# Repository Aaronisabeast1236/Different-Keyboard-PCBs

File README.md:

All of these files contain different Kicad keyboard PCBs and Schematics.
None of the files have have a microcontroller in them so they can not simply be downloaded and sent off to get printed, however they are ready for someone to put in and wire up a microcontroller
I am making these files because I could not find any templates online so I just decided to learn how to do it myself and share them with other people.
At some point I'd like to take suggestions and eventually add them to this repsitory.

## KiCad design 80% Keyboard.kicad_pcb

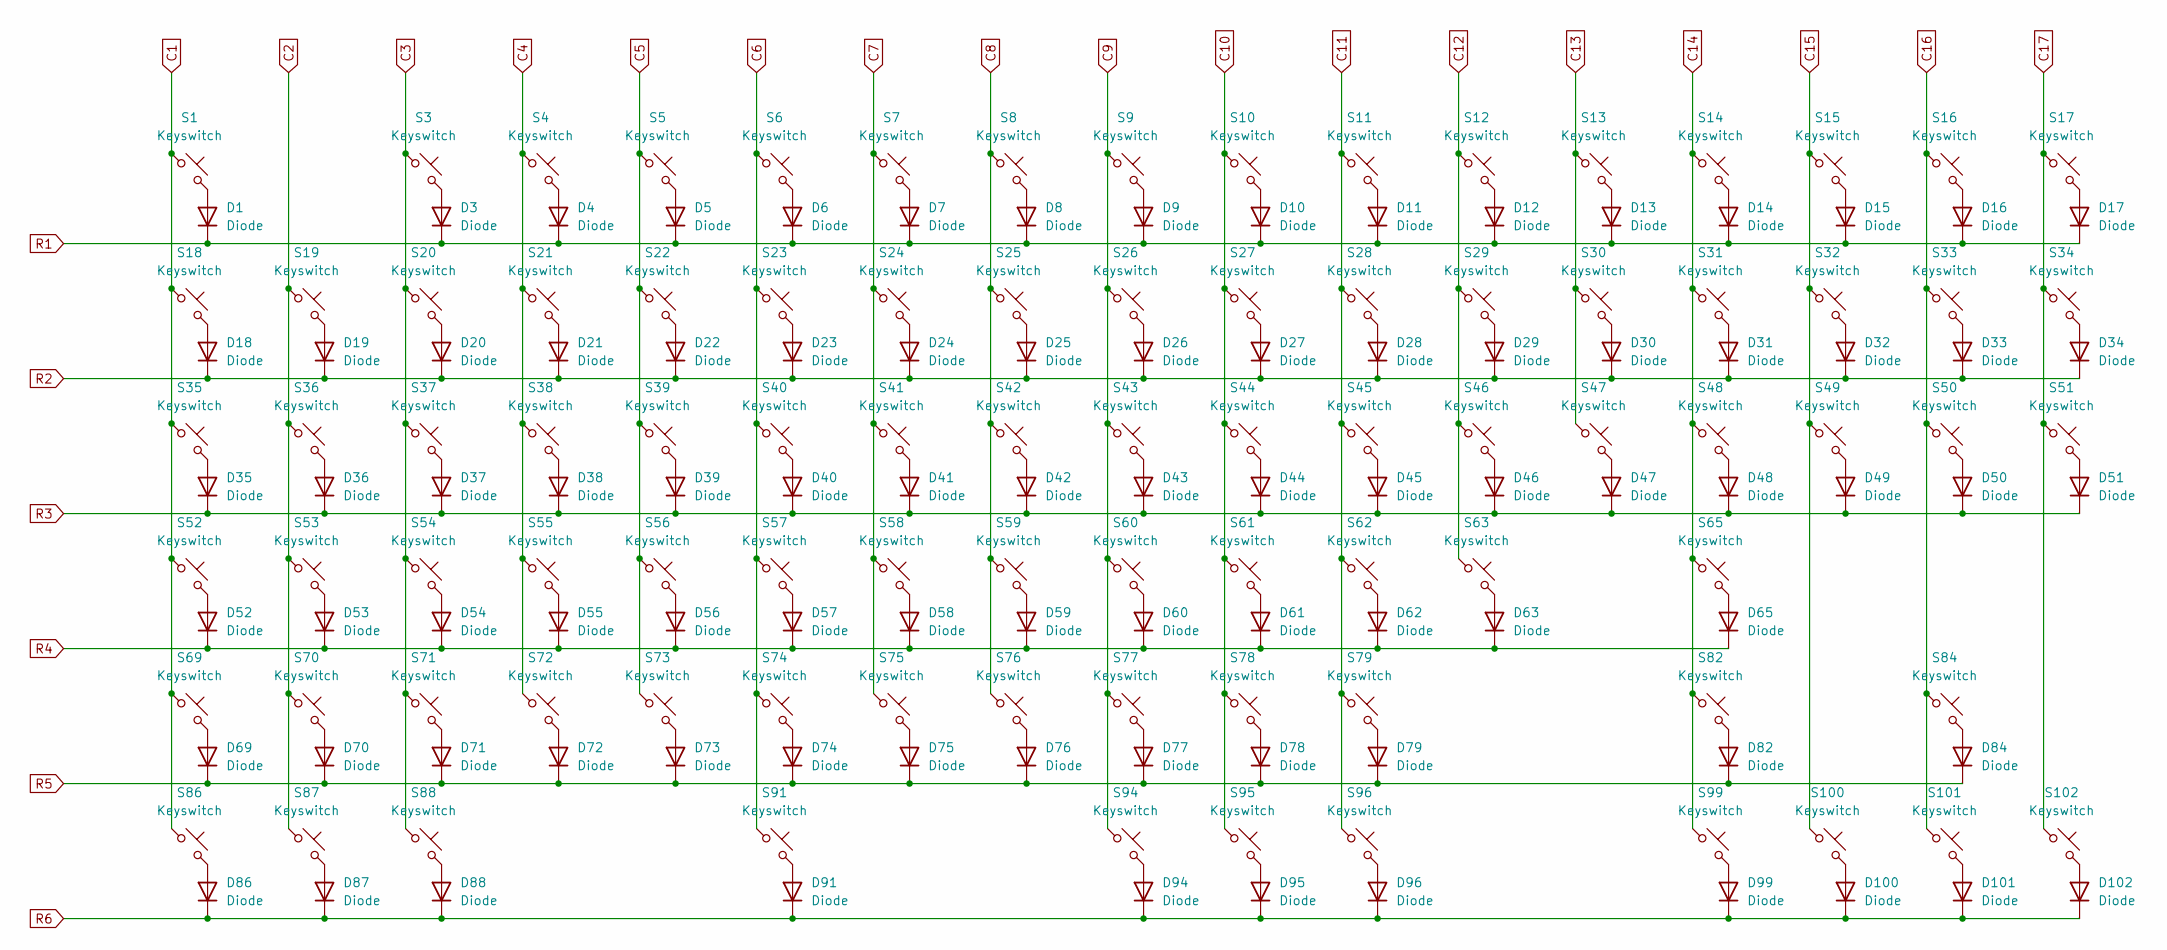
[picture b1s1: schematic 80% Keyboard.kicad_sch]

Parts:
D1, D3, D4, D5, D6, D7, D8, D9, D10, D11, D12, D13, D14, D15, D16, D17, D18, D19, D20, D21, D22, D23, D24, D25, D26, D27, D28, D29, D30, D31, D32, D33, D34, D35, D36, D37, D38, D39, D40, D41, D42, D43, D44, D45, D46, D47, D48, D49, D50, D51, D52, D53, D54, D55, D56, D57, D58, D59, D60, D61, D62, D63, D65, D69, D70, D71, D72, D73, D74, D75, D76, D77, D78, D79, D82, D84, D86, D87, D88, D91, D94, D95, D96, D99, D100, D101, D102: Diode; Diode_SOD-123
S1, S3, S4, S5, S6, S7, S8, S9, S10, S11, S12, S13, S14, S15, S16, S17, S18, S19, S20, S21, S22, S23, S24, S25, S26, S27, S28, S29, S30, S32, S33, S34, S36, S37, S38, S39, S40, S41, S42, S43, S44, S45, S46, S47, S49, S50, S51, S53, S54, S55, S56, S57, S58, S59, S60, S61, S62, S63, S70, S71, S72, S73, S74, S75, S76, S77, S78, S79, S84, S100, S101, S102: Keyswitch; MX_PCB_1.00u
S31: Keyswitch; MX_PCB_2.00u
S35, S48: Keyswitch; MX_PCB_1.50u
S52: Keyswitch; MX_PCB_1.75u
S65, S69: Keyswitch; MX_PCB_2.25u
S82: Keyswitch; MX_PCB_2.75u
S86, S87, S88, S94, S95, S96, S99: Keyswitch; MX_PCB_1.25u
S91: Keyswitch; MX_PCB_6.25u

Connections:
unnamed: D1.2 (A), S1.2
unnamed: D1.1 (K), D3.1 (K), D4.1 (K), D5.1 (K), D6.1 (K), D7.1 (K), D8.1 (K), D9.1 (K), D10.1 (K), D11.1 (K), D12.1 (K), D13.1 (K), D14.1 (K), D15.1 (K), D16.1 (K), D17.1 (K)
unnamed: D3.2 (A), S3.2
unnamed: D4.2 (A), S4.2
unnamed: D5.2 (A), S5.2
unnamed: D6.2 (A), S6.2
unnamed: D7.2 (A), S7.2
unnamed: D8.2 (A), S8.2
unnamed: D9.2 (A), S9.2
unnamed: D10.2 (A), S10.2
unnamed: D11.2 (A), S11.2
unnamed: D12.2 (A), S12.2
unnamed: D13.2 (A), S13.2
unnamed: D14.2 (A), S14.2
unnamed: D15.2 (A), S15.2
unnamed: D16.2 (A), S16.2
unnamed: D17.2 (A), S17.2
unnamed: D18.2 (A), S18.2
unnamed: D18.1 (K), D19.1 (K), D20.1 (K), D21.1 (K), D22.1 (K), D23.1 (K), D24.1 (K), D25.1 (K), D26.1 (K), D27.1 (K), D28.1 (K), D29.1 (K), D30.1 (K), D31.1 (K), D32.1 (K), D33.1 (K), D34.1 (K)
unnamed: D19.2 (A), S19.2
unnamed: D20.2 (A), S20.2
unnamed: D21.2 (A), S21.2
unnamed: D22.2 (A), S22.2
unnamed: D23.2 (A), S23.2
unnamed: D24.2 (A), S24.2
unnamed: D25.2 (A), S25.2
unnamed: D26.2 (A), S26.2
unnamed: D27.2 (A), S27.2
unnamed: D28.2 (A), S28.2
unnamed: D29.2 (A), S29.2
unnamed: D30.2 (A), S30.2
unnamed: D31.2 (A), S31.2
unnamed: D32.2 (A), S32.2
unnamed: D33.2 (A), S33.2
unnamed: D34.2 (A), S34.2
unnamed: D35.2 (A), S35.2
unnamed: D35.1 (K), D36.1 (K), D37.1 (K), D38.1 (K), D39.1 (K), D40.1 (K), D41.1 (K), D42.1 (K), D43.1 (K), D44.1 (K), D45.1 (K), D46.1 (K), D47.1 (K), D48.1 (K), D49.1 (K), D50.1 (K), D51.1 (K)
unnamed: D36.2 (A), S36.2
unnamed: D37.2 (A), S37.2
unnamed: D38.2 (A), S38.2
unnamed: D39.2 (A), S39.2
unnamed: D40.2 (A), S40.2
unnamed: D41.2 (A), S41.2
unnamed: D42.2 (A), S42.2
unnamed: D43.2 (A), S43.2
unnamed: D44.2 (A), S44.2
unnamed: D45.2 (A), S45.2
unnamed: D46.2 (A), S46.2
unnamed: D47.2 (A), S47.2
unnamed: D48.2 (A), S48.2
unnamed: D49.2 (A), S49.2
unnamed: D50.2 (A), S50.2
unnamed: D51.2 (A), S51.2
unnamed: D52.2 (A), S52.2
unnamed: D52.1 (K), D53.1 (K), D54.1 (K), D55.1 (K), D56.1 (K), D57.1 (K), D58.1 (K), D59.1 (K), D60.1 (K), D61.1 (K), D62.1 (K), D63.1 (K), D65.1 (K)
unnamed: D53.2 (A), S53.2
unnamed: D54.2 (A), S54.2
unnamed: D55.2 (A), S55.2
unnamed: D56.2 (A), S56.2
unnamed: D57.2 (A), S57.2
unnamed: D58.2 (A), S58.2
unnamed: D59.2 (A), S59.2
unnamed: D60.2 (A), S60.2
unnamed: D61.2 (A), S61.2
unnamed: D62.2 (A), S62.2
unnamed: D63.2 (A), S63.2
unnamed: D65.2 (A), S65.2
unnamed: D69.2 (A), S69.2
unnamed: D69.1 (K), D70.1 (K), D71.1 (K), D72.1 (K), D73.1 (K), D74.1 (K), D75.1 (K), D76.1 (K), D77.1 (K), D78.1 (K), D79.1 (K), D82.1 (K), D84.1 (K)
unnamed: D70.2 (A), S70.2
unnamed: D71.2 (A), S71.2
unnamed: D72.2 (A), S72.2
unnamed: D73.2 (A), S73.2
unnamed: D74.2 (A), S74.2
unnamed: D75.2 (A), S75.2
unnamed: D76.2 (A), S76.2
unnamed: D77.2 (A), S77.2
unnamed: D78.2 (A), S78.2
unnamed: D79.2 (A), S79.2
unnamed: D82.2 (A), S82.2
unnamed: D84.2 (A), S84.2
unnamed: D86.2 (A), S86.2
unnamed: D87.2 (A), S87.2
unnamed: D88.2 (A), S88.2
unnamed: D91.2 (A), S91.2
unnamed: D94.2 (A), S94.2
unnamed: D95.2 (A), S95.2
unnamed: D96.2 (A), S96.2
unnamed: D99.2 (A), S99.2
unnamed: D100.2 (A), S100.2
unnamed: D86.1 (K), D87.1 (K), D88.1 (K), D91.1 (K), D94.1 (K), D95.1 (K), D96.1 (K), D99.1 (K), D100.1 (K), D101.1 (K), D102.1 (K)
unnamed: D101.2 (A), S101.2
unnamed: D102.2 (A), S102.2
unnamed: S1.1, S18.1, S35.1, S52.1, S69.1, S86.1
unnamed: S10.1, S27.1, S44.1, S61.1, S78.1, S95.1
unnamed: S11.1, S28.1, S45.1, S62.1, S79.1, S96.1
unnamed: S12.1, S29.1, S46.1, S63.1
unnamed: S13.1, S30.1, S47.1
unnamed: S14.1, S31.1, S48.1, S65.1, S82.1, S99.1
unnamed: S19.1, S36.1, S53.1, S70.1, S87.1
unnamed: S3.1, S20.1, S37.1, S54.1, S71.1, S88.1
unnamed: S4.1, S21.1, S38.1, S55.1, S72.1
unnamed: S5.1, S22.1, S39.1, S56.1, S73.1
unnamed: S6.1, S23.1, S40.1, S57.1, S74.1, S91.1
unnamed: S7.1, S24.1, S41.1, S58.1, S75.1
unnamed: S8.1, S25.1, S42.1, S59.1, S76.1
unnamed: S9.1, S26.1, S43.1, S60.1, S77.1, S94.1
unnamed: S15.1, S32.1, S49.1, S100.1
unnamed: S16.1, S33.1, S50.1, S84.1, S101.1
unnamed: S17.1, S34.1, S51.1, S102.1

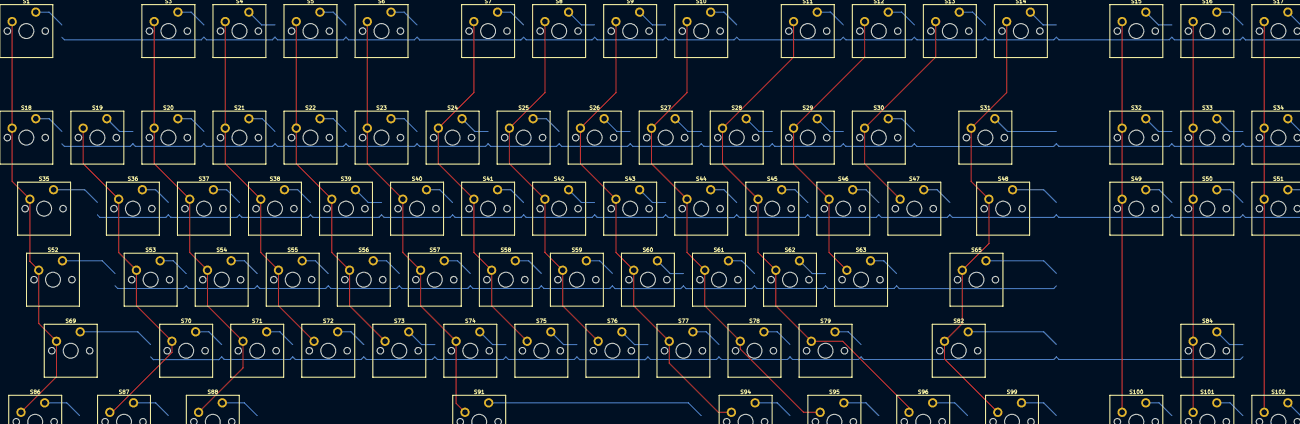
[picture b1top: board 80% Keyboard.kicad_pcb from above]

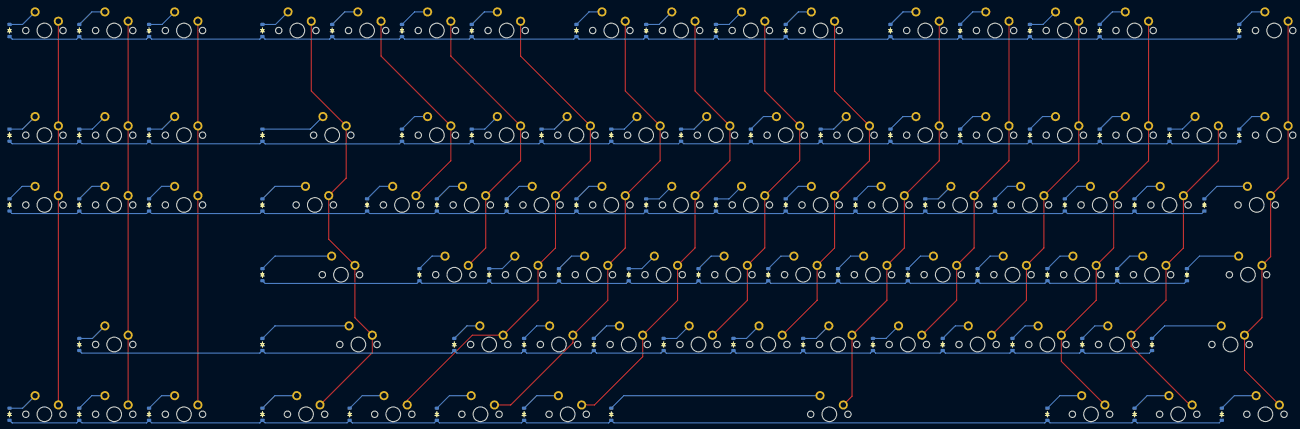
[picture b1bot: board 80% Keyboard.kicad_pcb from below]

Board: 2 copper layers, 174 parts (87 on the bottom side), 110 nets.

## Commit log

2025-06-24 Added 60% Keyboard Files
2025-06-25 Added 100% Keyboard Files
